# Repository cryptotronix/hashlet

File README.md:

Cryptotronix Hashlet
=====

Getting
---

The easiest way to install hashlet right now is to add my debian [repository](http://debian.cryptotronix.com/) and then just:

```
sudo apt-get update
sudo apt-get install hashlet
```

However, I've only packaged the binary for ARMv7. If you want to help package a binary for another system, I'd appreciate the help!

The second easiest way to install the software is to download the latest [release](http://download.savannah.gnu.org/releases/hashlet/hashlet-1.1.0.tar.gz) and then:

```
./configure && make
sudo make install
```

If you want to hack on hashlet, read more about building below.

Building
----

This project uses Autotools and you need that installed to configure and build the executable.  I am mainly developing on a BeagleBone Black using Debian.

If you pull this repo (i.e. a non-release), you will need the following dependencies:
- autotools (i.e. automake, autconf, and libtool)
- Flex and Bison
- texinfo (for the documentation if you so desire)

The run time dependencies are:
- libgcrypt

Hardware
---

The hardware was available from [Cryptotronix](http://cryptotronix.com/products/hashlet/).  We are an open hardware company, so see the `hardware` folder for the design to make this yourself. However, this software should work on any board that has an ATSHA204 in the I2C variety.

Running
---

see `./hashlet --help` for full details.  The default I2C bus is `/dev/i2c-1` and this can be changed with the `-b` option.  On some BBB, the bus is `/dev/i2c-2`.  See this [blog post](http://datko.net/2013/11/03/bbb_i2c/) for further details on BBB I2C.

Root
---

You'll need to run as root to access `/dev/i2c*` initially.  You can change this by adding your user to the `i2c` group with:

`sudo usermod -aG i2c user`

Or:

`sudo chmod o+rw /dev/i2c*`

Currently supported commands:

### state
```bash
./hashlet state
Factory
```

This is the first command you should run and verify it's in the Factory state.  This provides the assurance that the device has not been tampered during transit.

### personalize
```bash
./hashlet personalize
```

With the key import feature:

```bash
./hashlet personalize -f keys.txt
```

This is the second command you should run.  On success it will not output anything.  Random keys are loaded into the device and saved to `~/.hashlet` as a backup.  Don't lose that file.  Keys from another hashlet can be imported with the `-f` option, where the file is not also named `~/.hashlet`.

### random
```bash
./hashlet random
62F95589AC76855A8F9204C9C6B8B85F06E6477D17C3888266AEE8E1CBD65319
```

This command also takes the `-B` parameter which allows you to specify the number of bytes you want back from the random number generator.

### mac
```bash
./hashlet mac --file test.txt
mac       : C3466ABB8640B50938B260E17D86489D0EBB3F9C8009024683CB225FFFD3B4E4
challenge : 9F0751C90770E6B40E34BA8E06EFE453FAA46B5FB26925FFBD664FAF951D000A
meta      : 08000000000000000000000000
```

On success it will output three parameters:

1. mac: (aka challenge response) The result of the operation
2. challenge: This is the input to the Hashlet, after a SHA256 digest
3. meta: Meta data that must accompany the result

### check-mac
```bash
./hashlet check-mac -r C3466ABB8640B50938B260E17D86489D0EBB3F9C8009024683CB225FFFD3B4E4 -c 9F0751C90770E6B40E34BA8E06EFE453FAA46B5FB26925FFBD664FAF951D000A -m 08000000000000000000000000
```

Checks the MAC that was produced by the Hashlet.  On success, it will with an exit value of 0.

### offline-verify
```bash
./hashlet offline-verify -c 322B3FFC3BE16B4CC5B445F8E666D0BA5C5E676D00FABD2308AD51243FA0B067 -r FB19B1C63161B6C34CA9D291D1CD16F98247BBA9A298775F795161BEB95BB6EF
```

On success, it will output an exit code of 0, otherwise it will fail.  The point of this command is that a remote server can verify the MAC from the Hashlet without a device.  The keys are written to `~/.hashlet` upon personalization and if this file is store on the server, it can verify a MAC.

The workflow goes like this:

1. Mac some data to produce a challenge response.
2. Send the challenge and MAC to the remote server, which has the key store file.
3. Perform offline-verify on the remote server.

### hmac
```bash
hashlet hmac -f ChangeLog
CD0765AB1F94698E0EACDE22C10F362E925F4F4017B75FDE5AB3124FCEBE9754
```
```bash
echo test | ./hashlet hmac
9CAF53A19F4A8D751F9D03ED3991EF648DC9246D2B329D9A650307212D994326
```

Performs HMAC-256. Your input data is combined with data on the device, so this isn't a pure HMAC-256. Your data will be applied to SHA-256 and then combined, per the datasheet, with device data. That result is fed into HMAC-256.

### offline-hmac
```bash
hashlet offline-hmac -r CD0765AB1F94698E0EACDE22C10F362E925F4F4017B75FDE5AB3124FCEBE9754 -f ChangeLog
echo $?
0
```
```bash
echo test | ./hashlet offline-hmac -r 9CAF53A19F4A8D751F9D03ED3991EF648DC9246D2B329D9A650307212D994326
echo $?
0
```

Similar to `offline-verify`, verifies the hmac operation using the key file from `~/.hashlet`.
### serial-num
```bash
./hashlet serial-num
0123XXXXXXXXXXXXEE
```
X's indicate the unique serial number.

Options
---

Options are listed in the `--help` command, but a useful one, if there are issues, is the `-v` option.  This will dump all the data that
travels across the I2C bus with the device.

Design
---

In the `hardware` folder, one should find the design files for the Hashlet.  The IC on the hashlet is the [Atmel ATSHA204](http://www.atmel.com/Images/Atmel-8740-CryptoAuth-ATSHA204-Datasheet.pdf).

Support
---

IRC: Join the `#cryptotronix` channel on freenode.

Contributing
---
Pull requests welcome :)

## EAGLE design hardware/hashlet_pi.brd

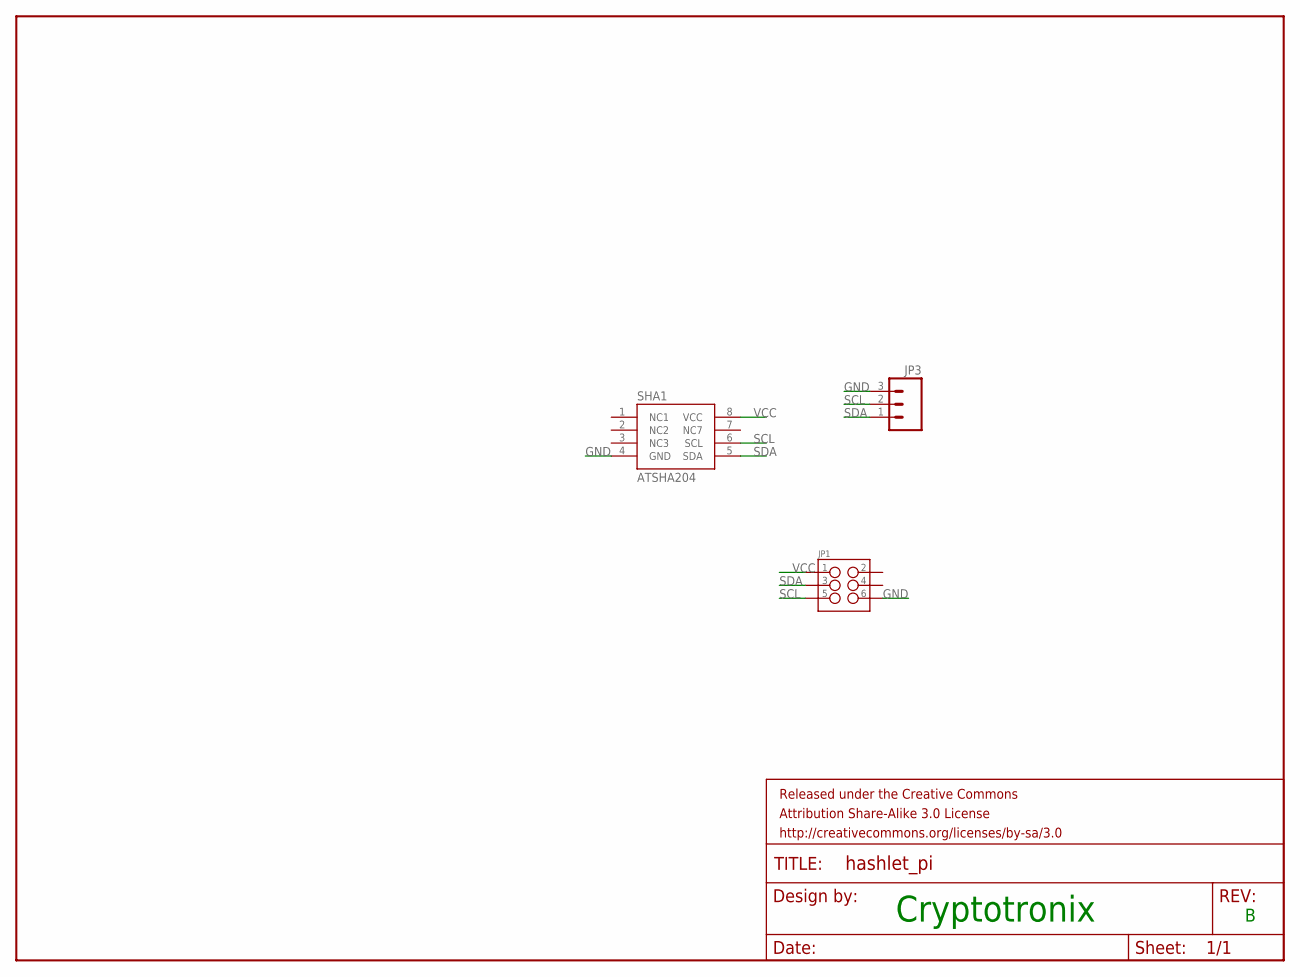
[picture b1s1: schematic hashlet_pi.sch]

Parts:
FRAME1: FRAME-LETTER; CREATIVE_COMMONS
JP1: M03X22X3_SILK_SM; 2X3
JP3: M03PTH; 1X03
SHA1: ATSHA204; SOIC8

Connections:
GND: JP1.6, JP3.3, SHA1.4 (GND)
SCL: JP1.5, JP3.2, SHA1.6 (SCL)
SDA: JP1.3, JP3.1, SHA1.5 (SDA)
VCC: JP1.1, SHA1.8 (VCC)

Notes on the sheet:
Cryptotronix

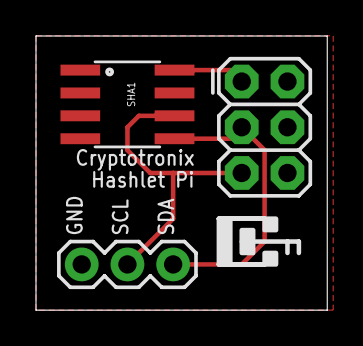
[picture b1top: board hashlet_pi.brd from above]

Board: 2 copper layers, 16.2 x 15.2 mm, 4 parts (0 on the bottom side), 4 nets.

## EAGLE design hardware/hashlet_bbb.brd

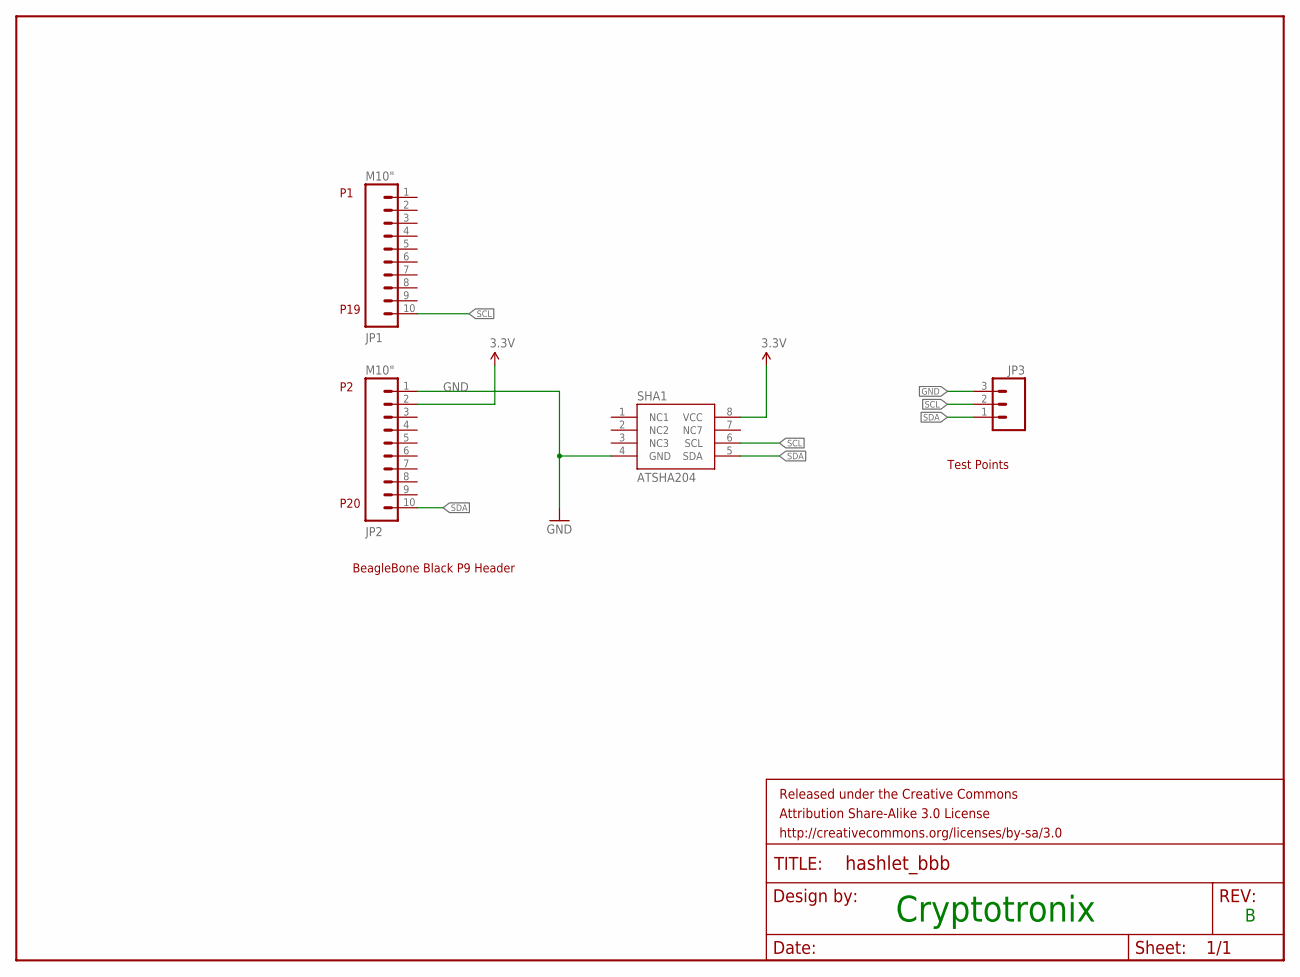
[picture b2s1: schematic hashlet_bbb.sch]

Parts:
FRAME1: FRAME-LETTER; CREATIVE_COMMONS
JP1, JP2: M10"; 1X10
JP3: M03PTH; 1X03
SHA1: ATSHA204; SOIC8

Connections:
3.3V: JP2.2, SHA1.8 (VCC)
GND: JP2.1, JP3.3, SHA1.4 (GND)
SCL: JP1.10, JP3.2, SHA1.6 (SCL)
SDA: JP2.10, JP3.1, SHA1.5 (SDA)

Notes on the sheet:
Cryptotronix
BeagleBone Black P9 Header
Test Points
P19
P20

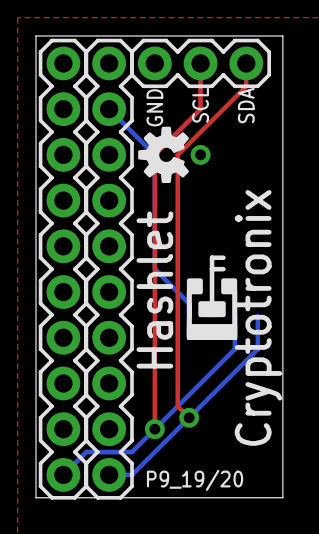
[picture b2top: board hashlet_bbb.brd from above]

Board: 2 copper layers, 13.7 x 25.7 mm, 6 parts (1 on the bottom side), 4 nets.

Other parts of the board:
U$1: OSHW-LOGO-S

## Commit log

2013-12-11 Initial. It begins...
2013-12-11 Updated ignore with autotools generated files.
2013-12-11 Added pdf of schematic.
2013-12-13 Add TAGS to .gitignore. Emacs FTW.
2013-12-13 Added basic logging.
2013-12-13 i2c cleanup.
2013-12-13 Whitespace cleanup.
2013-12-13 Changed wakeup return value.
2013-12-13 Added basic fd check on i2c_open.
2013-12-13 Added get_config_data.
2013-12-13 slowly cleaning up debug.
2013-12-14 Fix autotools message. Resolves #1.
2013-12-16 Added compile to gitignore.
2013-12-16 Added lock command, which is working only for the config section at the moment.
2013-12-16 Eliminated compiler warnings. Resolves #2.
2013-12-16 Updated readme. We are now in Alpha!
2013-12-16 Emacs un-fill destroyed the markup. Fixed.
2013-12-18 Added basic code for setting OTP zone #4.
2013-12-18 Commented out locking the configuration zone.
2013-12-18 Set the OTP Mode to Read Only. Resolves #7.
2013-12-18 Fixed compile warnings.
2013-12-18 Add .deps directory
2013-12-18 Trying to bend Automake to my will and failing.
2013-12-18 Fixed slot config configuration.
2013-12-18 Corrected bit masks.
2013-12-19 Added guards around setting the config zone.
2013-12-19 Added write32 and set OTP zone.
2013-12-19 Refactored get_random
2013-12-19 Added basic write32 and writing keys to data section.
2013-12-19 Hardcoded MAC check is working!
2013-12-19 Removed hard coded values in mac and write32. Fixed Get_serial_num.
2013-12-19 Made the hash test a bit more modular.
2013-12-20 Added read32
2013-12-20 Added basic CLI for get random command for issue #6.
2013-12-20 Updated running section with an example.
2013-12-20 Markdown tweaks.
2013-12-20 Added command for getting the serial number.
2013-12-20 Credited the bithacks site for the reverse function. This code snippet is listed in the public domain on that site.
2013-12-20 Added link to contributing page.
2013-12-20 Added disclaimer about the state of the software.
2013-12-20 I need to default this buffer to not auto-fill...
2013-12-20 Added check on malloc.
2013-12-21 Added parse slot config.
2013-12-21 Left blank TODO for slot-config.
2013-12-21 Refactored directory structure
2013-12-21 Added cflags. I'm still not sure why these are carried forward from configure.ac
2013-12-22 Added macro for repeated code. Added get-config zone command.
2013-12-22 Formatting changes.
2013-12-22 Added check_mac function, but untested!
2013-12-22 Moved tests to their own directory.
2013-12-23 Formatting changes only.
2013-12-23 Added check for gnutls version for issue #9
2013-12-23 Fixed formatting.
2013-12-23 Fixed formatting to the correct style.
2013-12-23 Whitespace changes.
2013-12-23 More whitespace changes.
2013-12-23 Refactored i2c send and receive command which should resolve #3.
2013-12-23 Removed tests that required GnuTLS. Perhaps a better way is to make a test app that builds with GnuTLS only with make check. Resolves #9.
2013-12-23 Implemented get-state command.
2013-12-24 Personalization appears complete. Need to test with a fresh device. Resloves #4.
2013-12-24 Added placeholders for mac and check-mac for issue #11.
2013-12-24 Fixed compile errors from compiling on a 64 bit Ubuntu machine.
2013-12-26 Added initial unit tests for #14.
2013-12-26 Added the MAC command to take in an arbitrary length file. This depends on libgcrypt to guarantee a 32 byte available. Another way to do this is to not directly depend on an external hash implementat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
    If libgcrypt is not available, this feature will be not be enabled.
2013-12-26 Refactored command line dispatcher.
2013-12-26 Add option to read input from file.
    Adds input file option, good suggestion. I picked '-f' though [1],
    although I have seen '-i' before.
    [1] http://www.faqs.org/docs/artu/ch10s05.html
2013-12-27 Adds command for retrieving the OPT zone.
    Now supports retrieving otp zone via "get-otp" from the CLI.
2013-12-27 Adds parsing feature for key files.
    Adds parsing feature for generated and stored key_slot_files. Uses the
    grammar defined in the flex and bison files to parse key files. Changes
    the autotools setup files to accommodate flex and bison files. Adds a
    print_keys command, which may not make it in the final release, to test
    the parsing.
    The parser will be eventually needed in order to verify a MAC or HMAC on
2013-12-27 Adds offline-verify command.
    Adds the ability to verify a MAC produced on a Hashlet, without the
    hardware. This is useful when a remote server wants to verify the MAC,
    but doesn't have an attached hashlet.
2013-12-28 Fixes order of status packet checking for issue #13.
    Needs verification test.
2013-12-28 Adds const qualifiers on util functions.
2013-12-28 Adds check mac internals for issue #11.
    The MAC command now automatically performs a check mac to verify the
    mac (and meta data) are accurate.
2013-12-28 Adds check-mac from command line. Closes #11.
2013-12-29 Adds script to pull 20,000 bits of random data for rng-tool tests.
2013-12-29 Adds doc target to build with sample documentation
2013-12-29 Adds licenses to files.
2013-12-29 Adds gitignore
2013-12-29 Adds initial documentation.
2013-12-29 Adds node info to prevent compile error.
2013-12-30 Moves all configuration zone operations to config_zone.c and config_zone.h
2013-12-30 Fixes the fixed value of keys 14 and 15
2013-12-30 Fixs config zone setting and parsing for issue #19.
2013-12-30 Adds Travis CI hook.
2013-12-30 Attempt at fixing travis.
2013-12-30 Comments out AC_LOCAL_MACRO_DIR. Experimenting with Travis CI.
2013-12-30 Modifies travis ci script.
2013-12-30 Create m4 directory manually
2013-12-30 Adds install of texinfo to travis ci.
2013-12-30 Adds Travis CI status image.
2013-12-30 Fixes image url.
2013-12-30 Fixing url... again.
2013-12-30 Moves scripts into autogen.sh
2013-12-30 Adds aback AC_CONFIG_MACRO_DIR
2013-12-30 Adds documentation on config_zone.
2013-12-30 Fixes config zone per documentation. Closes #19, closes #13, closes #15.
2013-12-30 Adds missing switch case.
2013-12-30 Adds text file for documentation.
2013-12-30 Adds test cases for personalized hashlets. Resolves #14.
2013-12-30 Removes output file option as that is currently not implemented.
2013-12-30 Add useful script to convert git-logs to the ChangeLog
2013-12-30 Updates NEWS file for 0.1.0 release.
2013-12-30 Updates documentation to indicate Beta status.
2013-12-31 Adds test_cli to EXTRA_DIST
2013-12-31 Removes dvi target to prevent make distcheck failures.
2013-12-31 Adds check to exit successfully if not on a system with /dev/i2c-1.
2013-12-31 Updates INSTALL from recent version of autotools.
2013-12-31 Updates ChangeLog for version 0.1.0
2014-01-03 Adds support info and link to releases.
2014-01-03 Adds chapter on installing the hardware and software.
2014-01-03 Updates initial documentation for version 0.1.0.
2014-01-03 Adds schematic to figures.
2014-01-04 Changes menu chapter to hashlet from sample.
2014-01-21 Adds partial changes to write only key feature.
2014-01-21 Adds read and write commands to data slots.
2014-01-25 Adds debug around write.
2014-01-25 Fixes always succeeding write bug. Adds mac to write32.
2014-01-25 Changes key slots 6 and 7 to required encrypted writes.
2014-01-25 Updates signature for new write32.
2014-01-25 Adds nonce command. Resolves issue #17.
2014-01-26 Adds copy buffer utilities and xor utility.
2014-01-26 adds initial (broken) encrypted write feature.
2014-01-27 Adds infrastructure code for HMAC #25.
    Adds command line interface to route code to HMAC.
    Adds HMAC mac mode encoding structure.
    Adds perform_hmac function
    Adds serialize_hmac_mode function.
2014-01-27 Defaults bus to /dev/i2c-1
    Removes the required positional argument for the bus and defaults to
    /dev/i2c-1. Resolves issue #20.
2014-01-31 Adds factory tests
2014-02-02 adds board and sch files
2014-02-02 Adds attribution to board files
2014-02-02 Fixes doc errors and adds section on personalization. Resolves #26.
    Fixes minors typos.
    Adds email to GPG key and short fingerprint.
    Adds warning to personalization command.
2014-02-07 Adds clarifying error message to failed bus for issue #20.
2014-02-07 Adds key import feature. Resolves #15.
    Allows the option to clone the data zone from another device if the file
    is specified with the -f option. Currently the configuration zone is
    not cloned, just the data zone.
2014-02-07 Copies the response byte. Resolves issue #24.
2014-02-07 Always updates the seed. Resolves issue #30.
2014-02-07 Adds check-mac documentation. Resolves #22.
2014-02-07 Bumps version.
2014-02-07 Updates test to use -b option.
2014-02-07 Updated NEWS for release.
2014-02-07 Updates test to use a file that is available during make distcheck.
2014-02-07 libgcrypt is now required to build.
2014-02-07 Updates github documeation.
2014-02-07 Updates ChangeLog.
2014-02-07 Adds uname check to prevent running tests on none embedded systems.
2014-04-08 Adds new command to get a specified number of bytes - Dave Taht #31
2014-04-08 Remove extraneous message
2014-04-08 Get a minimum of 32 bytes
2014-04-08 Tidying
2014-04-08 Can return less than 32 bytes
2014-04-08 *2 no longer needed
2014-04-18 Adds coverity link.
2014-04-18 Adds projectile project file.
2014-04-18 Reverts to gnu coding style to be consistent with rest of project.
2014-04-18 Fixes errors found by coverity scan. Resolves #8.
2014-04-18 Merges get-random bytes into the random command.
    Adds the -B option to the random command so that there is only one
    random command from the cli.
2014-04-18 Updates contributing authors.
2014-04-18 Updates documentation.
2014-04-19 Adds HMAC command. Resolves #25.
2014-04-19 Adds documentation for HMAC command. #25.
2014-04-19 Updates tests for new features.
2014-04-19 Updates online help.
2014-04-19 Updates NEWS.
2014-10-29 Switches to kernel backend.
    Uses the alpha version of the kernel module.
2016-05-28 Removes libgcrypt depends.

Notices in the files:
parts and their libraries:
SparkFun-Connectors: Licensing: CC v3.0 Share-Alike You are welcome to use this library for commercial purposes.
SparkFun-Aesthetics: Released under the Creative Commons Attribution Share-Alike 3.0 License
SparkFun-Aesthetics: http://creativecommons.org/licenses/by-sa/3.0
